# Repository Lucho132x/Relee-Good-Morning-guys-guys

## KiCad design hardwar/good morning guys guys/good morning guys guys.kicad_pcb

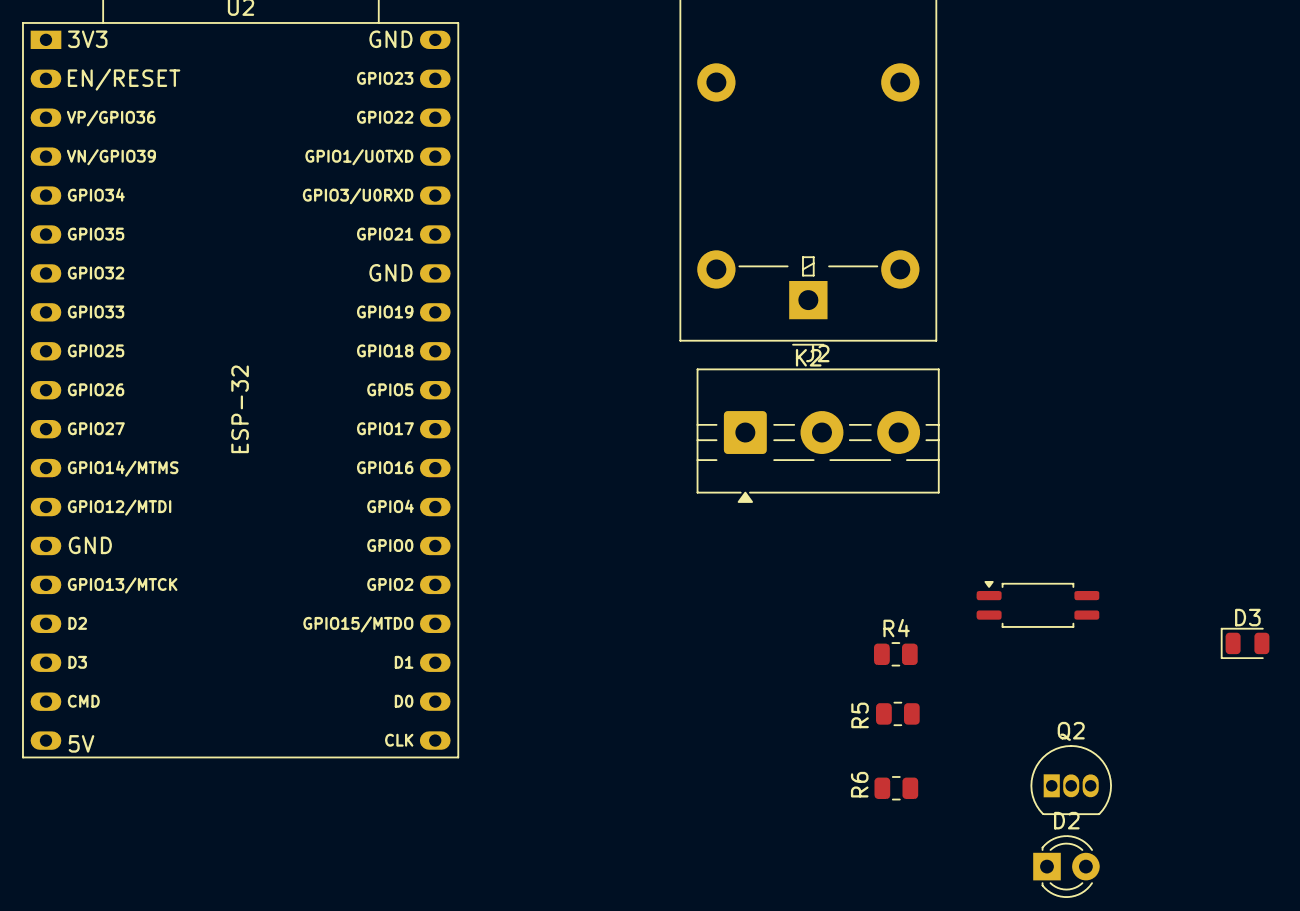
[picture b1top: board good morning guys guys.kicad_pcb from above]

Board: 2 copper layers, 10 parts (0 on the bottom side), 10 nets, no tracks yet.

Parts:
D2: LED; LED_D3.0mm_Clear
D3: 1N4007; D_0805_2012Metric
J2: Screw_Terminal_01x03; TerminalBlock_MaiXu_MX126-5.0-03P_1x03_P5.00mm
K2: G5LE-1; Relay_SPDT_Omron-G5LE-1
Q2: BC337; TO-92_Inline
R4: 330; R_0805_2012Metric
R5: 1K; R_0805_2012Metric
R6: 220; R_0805_2012Metric
U2: ESP-32; ESP32-DevKitC
U5: PC817; SOP-4_4.4x2.6mm_P1.27mm

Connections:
+5V: D3.1 (K), K2.5, R6.2, U5.4
/COM: J2.3, K2.1
/NC: J2.2, K2.3
/NO: J2.1, K2.4
GND: Q2.3 (E), U5.2
unnamed: D2.2 (A), R6.1
unnamed: D2.1 (K), D3.2 (A), K2.2, Q2.1 (C)
unnamed: Q2.2 (B), R5.2
unnamed: R4.2, U5.1
unnamed: R5.1, U5.3
